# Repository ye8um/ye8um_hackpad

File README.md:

# ye8um_hackpad
hackpad design for the Blueprint program

My hackpad design is a simple and modular pad you can use for performative work with three keys and a rotary encoder for volume control. 
Designed this project so that my setup can look cooler and be functional:D

BOM:

3x Cherry MX Keycaps

1x EC11 Rotary Encoder

4x M3x12mm SHCS Bolts

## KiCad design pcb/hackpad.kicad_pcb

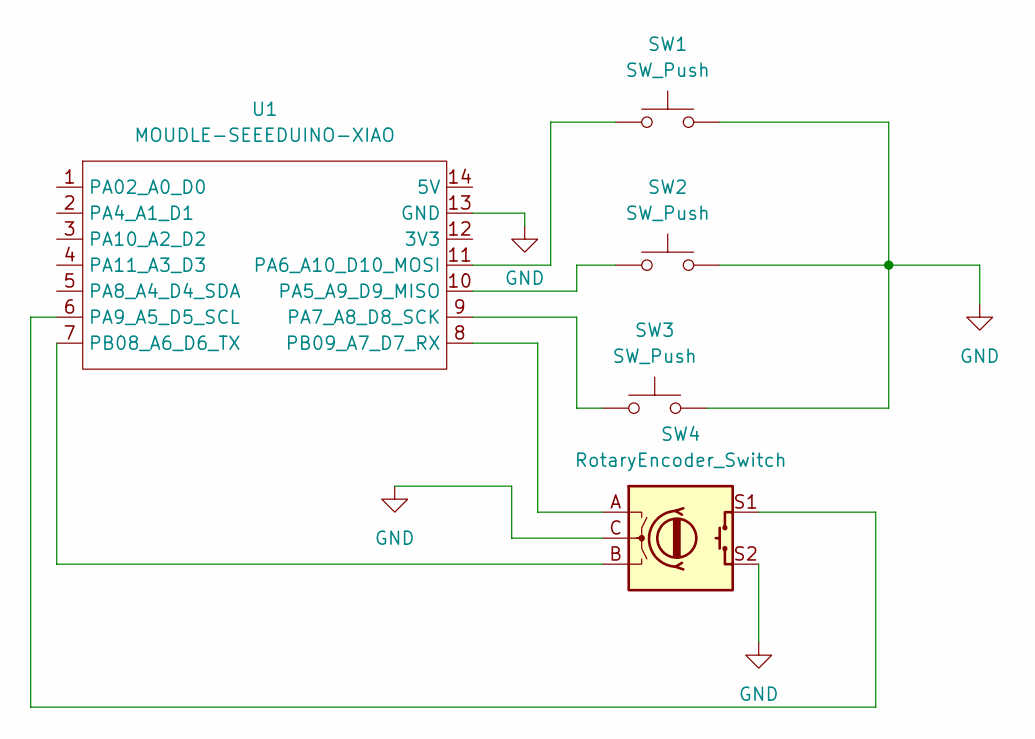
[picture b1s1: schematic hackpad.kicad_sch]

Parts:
SW1, SW2, SW3: SW_Push; SW_Cherry_MX_1.00u_PCB
SW4: RotaryEncoder_Switch; RotaryEncoder_Alps_EC11E-Switch_Vertical_H20mm
U1: MOUDLE-SEEEDUINO-XIAO; XIAO-Generic-Hybrid-14P-2.54-21X17.8MM

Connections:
GND: SW1.2, SW2.2, SW3.2, SW4.C, SW4.S2, U1.13 (GND)
unnamed: SW2.1, U1.10 (PA5_A9_D9_MISO)
unnamed: SW1.1, U1.11 (PA6_A10_D10_MOSI)
unnamed: SW3.1, U1.9 (PA7_A8_D8_SCK)
unnamed: SW4.S1, U1.6 (PA9_A5_D5_SCL)
unnamed: SW4.B, U1.7 (PB08_A6_D6_TX)
unnamed: SW4.A, U1.8 (PB09_A7_D7_RX)

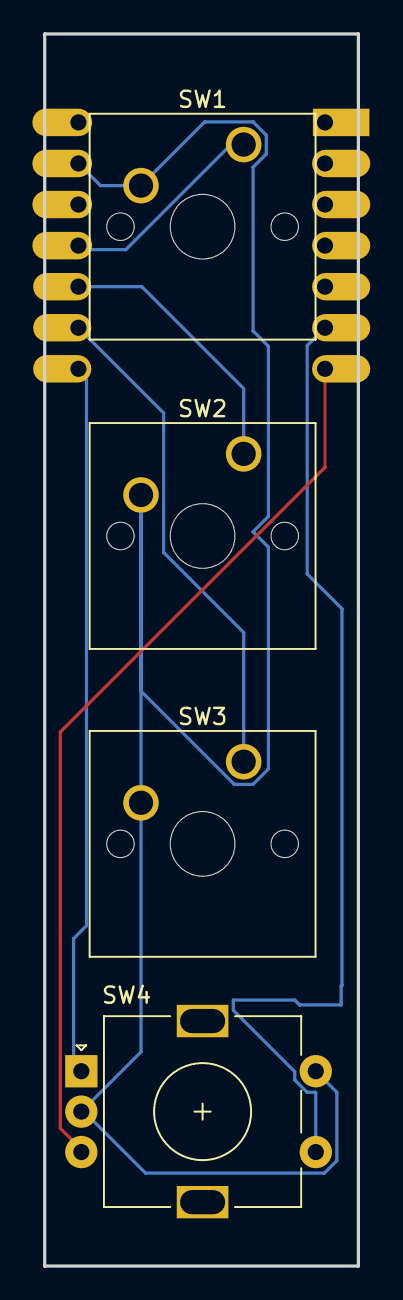
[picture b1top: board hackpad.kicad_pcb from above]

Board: 2 copper layers, 19.4 x 76.2 mm, 5 parts (1 on the bottom side), 7 nets.

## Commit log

2026-04-01 Add hackpad project files
2026-05-14 NewChanges
2026-05-14 PCB change
2026-05-15 Pcb connections
2026-05-15 edits
